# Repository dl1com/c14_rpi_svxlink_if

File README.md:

# c14_rpi_svxlink_if
Raspberry Pi Hat for SVXLink

This repository contains the code and instructions for a custom interface between radio transceivers and a Raspberry Pi running SVXLink.

## Repository contents
The repository contains the following files and directories:

* [c14_rpi_svxlink_if.kicad_pcb](./c14_rpi_svxlink_if.kicad_pcb): the KiCAD project for the custom PCB design.
* [LICENSE.md](./LICENSE.md): the license file for the repository (CC-BY-SA).
* README.md: this file.

## Features

The interface offers the following features:

* Generic DB9 connector for interfacing to transceiver(s)
* Isolated audio rx/tx and signal paths (PTT, Squelch)
* Audio levels can be set with potis
* Fan control output and tacho input
* Telemetry inputs:
  * ADS1115 ADC (i.e. for voltage or RSSI measurement)
  * I2C connectors (i.e. for temperature sensors)

We deliberately decided against placing a soundcard IC on the interface. We use an external, generic USB soundcard instead, as these type of soundcards are very easy and cheap to get on various market places.

## Signal mapping

### DB9 Connector

| Number | Name       |
| ------ | ---------- |
| 1      | SQL_DET-   |
| 2      | SQL_DET+   |
| 3      | RSSI       |
| 4      | RX_AUDIO- |
| 5      | RX_AUDIO+ |
| 6      | PTT_GND   |
| 7      | PTT+      |
| 8      | TX_AUDIO- |
| 9      | TX_AUDIO+ |

### RPi

| GPIO    | Pin | Function   |
| ------- | --- | ---------- |
| GPIO17  | 11  | PTT        |
| GPIO22  | 15  | SQL Det.   |
| GPIO18  | 12  | Fan Ctrl   |
| GPIO24  | 18  | Fan Tacho  |

### Jumper

| JP  | Function                |
| --- | ----------------------- |
| JP1 | Bypass PWM (always on)  |
| JP2 | Enable clipping diodes  |

## Usage

An example project which uses this board can be found at https://charly14.de/svxlink-installation-und-konfiguration/

## License
This repository is licensed under the CC-BY-SA. See the LICENSE file for details.

Concept ist based on the [SVXLink Interface by Aleksander, S65AL](http://lea.hamradio.si/~s57nan/ham_radio/svx_intf_rpi/svx_intf_rpi.html)

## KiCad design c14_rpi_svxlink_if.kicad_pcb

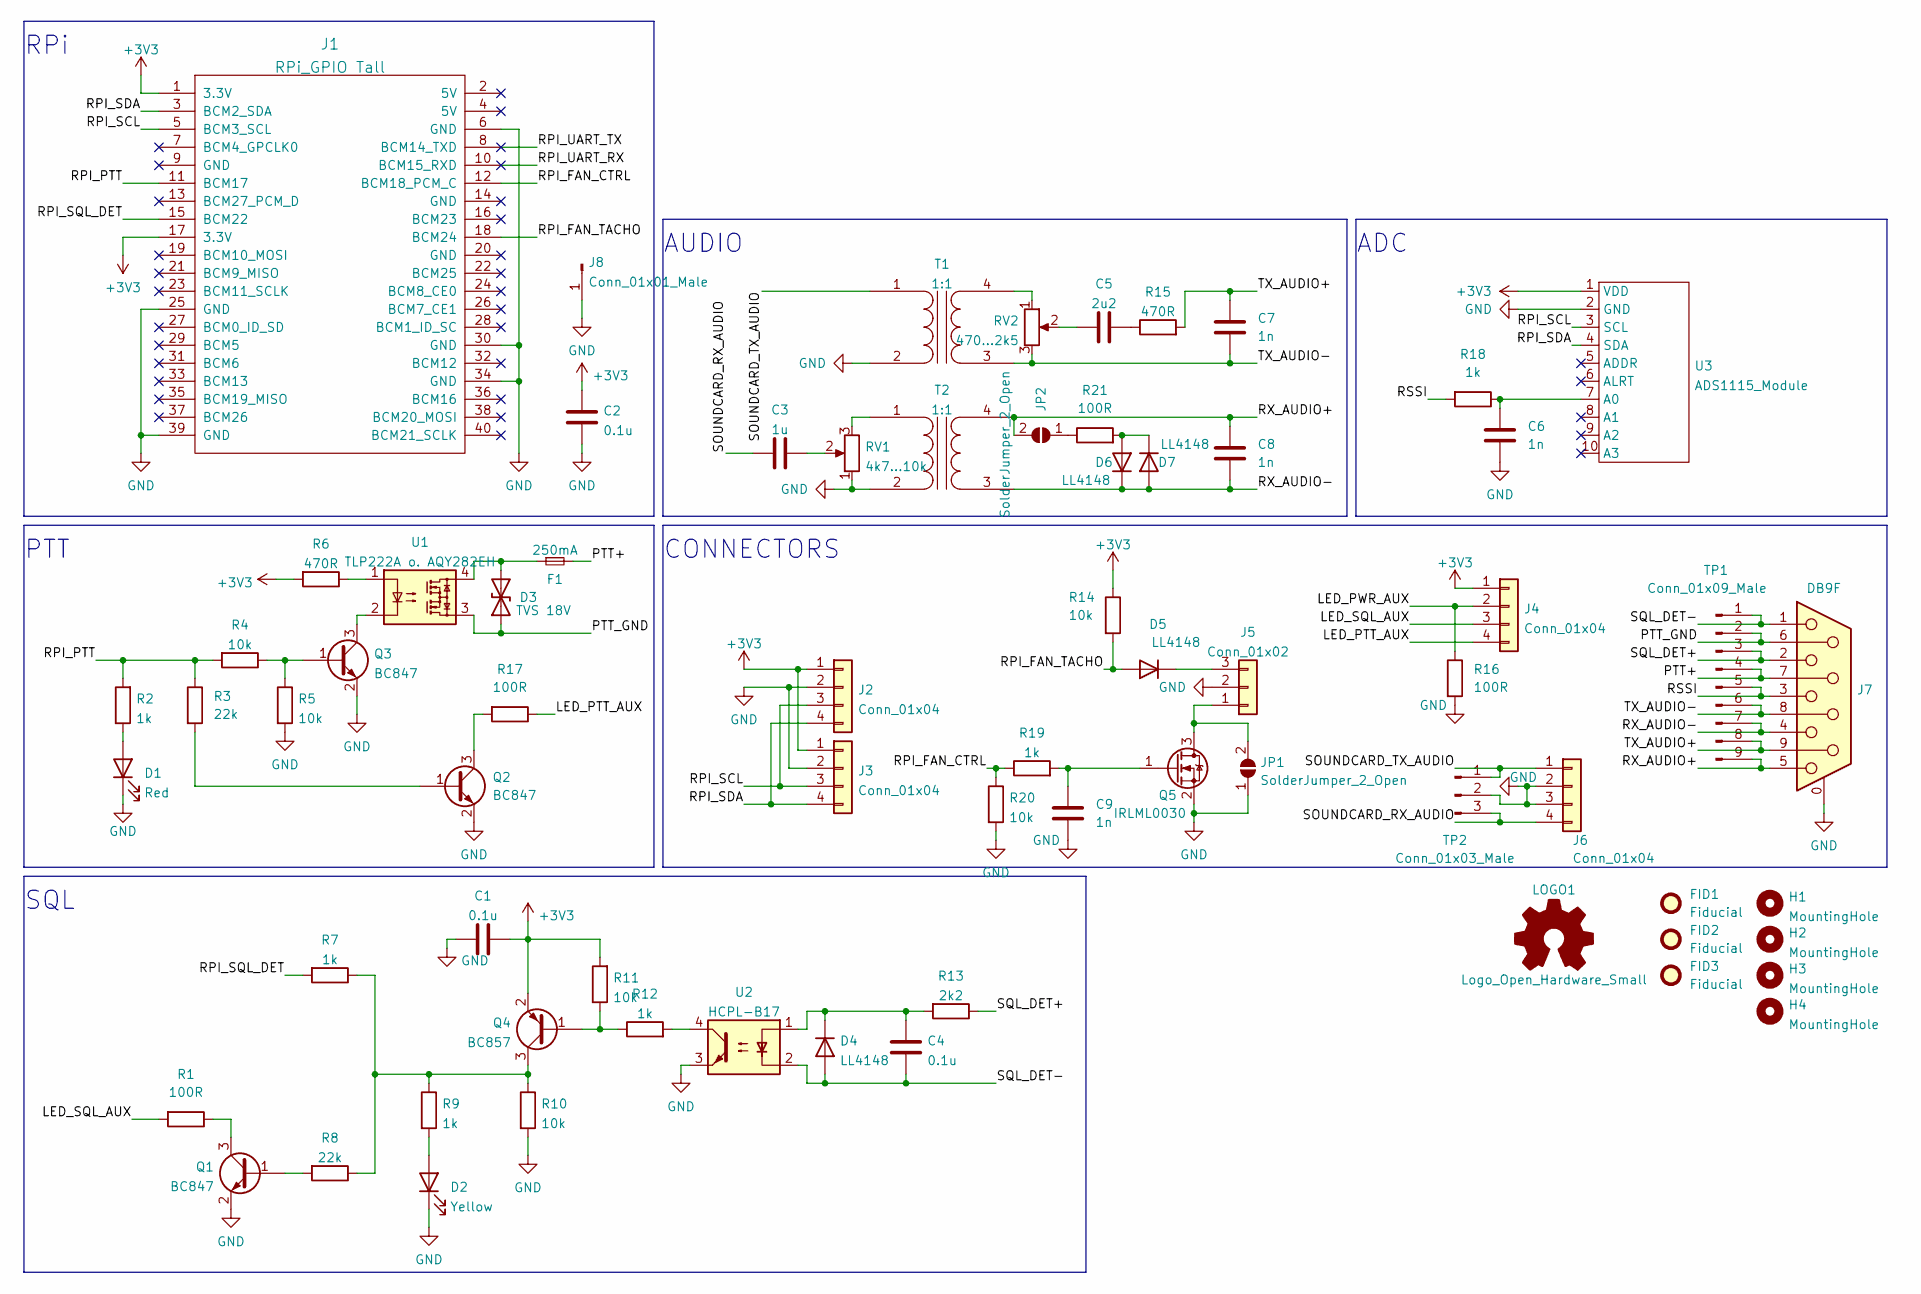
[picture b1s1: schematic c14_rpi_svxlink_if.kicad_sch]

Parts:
C1, C2, C4: 0.1u; C_0805_2012Metric_Pad1.18x1.45mm_HandSolder; PartNr_Mouser 603-CC805KRX7R9BB104
C3: 1u; C_Rect_L7.2mm_W4.5mm_P5.00mm_FKS2_FKP2_MKS2_MKP2; PartNr_Mouser 871-B32529C105J189
C5: 2u2; C_Rect_L7.2mm_W8.5mm_P5.00mm_FKP2_FKP2_MKS2_MKP2; PartNr_Mouser 80-R82CC4220Z370J
C6, C7, C8, C9: 1n; C_0805_2012Metric_Pad1.18x1.45mm_HandSolder; PartNr_Mouser 187-CL21B102KBANNNL
D1: Red; LED_0805_2012Metric_Pad1.15x1.40mm_HandSolder; PartNr_Mouser 755-SML-H12V8TT86C
D2: Yellow; LED_0805_2012Metric_Pad1.15x1.40mm_HandSolder; PartNr_Mouser 755-SML-H12Y8TT86C
D3: TVS 18V; D_SMA-SMB_Universal_Handsoldering; PartNr_Mouser 494-SMBJ18CAE3/TR13
D4, D5, D6, D7: LL4148; D_MiniMELF; PartNr_Mouser 512-LL4148
F1: 250mA; Fuse_1206_3216Metric_Pad1.42x1.75mm_HandSolder; PartNr_Mouser 576-1206L025YR
FID1, FID2, FID3: Fiducial; Fiducial_1mm_Mask3mm
H1, H2, H3, H4: MountingHole; RPi_Hat_Mounting_Hole; PartNr_Mouser --
J1: RPi_GPIO Tall; Pin_Header_Straight_2x20; PartNr_Mouser 485-1992
J2, J3, J4, J6: Conn_01x04; JST_XH_B4B-XH-A_1x04_P2.50mm_Vertical; PartNr_Mouser --
J5: Conn_01x02; JST_XH_B3B-XH-A_1x03_P2.50mm_Vertical
J7: DB9F; DSUB-9_Female_Horizontal_P2.77x2.84mm_EdgePinOffset7.70mm_H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; PartNr_Mouser 523-L77SDE09SA4CH3F
J8: Conn_01x01_Male; PinHeader_1x01_P2.54mm_Vertical
JP1, JP2: SolderJumper_2_Open; SolderJumper-2_P1.3mm_Open_TrianglePad1.0x1.5mm
LOGO1: Logo_Open_Hardware_Small; OSHW-Logo2_9.8x8mm_SilkScreen
Q1, Q2, Q3: BC847; SOT-23; PartNr_Mouser 771-BC847235
Q4: BC857; SOT-23; PartNr_Mouser 771-BC857/T3
Q5: IRLML0030; SOT-23; PartNr_Mouser 942-IRLML0030TRPBF
R1, R16, R17, R21: 100R; R_0805_2012Metric_Pad1.20x1.40mm_HandSolder; PartNr_Mouser 603-RC0805JR-07100RL
R2, R7, R9, R12, R18, R19: 1k; R_0805_2012Metric_Pad1.20x1.40mm_HandSolder; PartNr_Mouser 652-CR0805FX-1001ELF
R3, R8: 22k; R_0805_2012Metric_Pad1.20x1.40mm_HandSolder; PartNr_Mouser 603-RC0805FR-0722KL
R4, R5, R10, R11, R14, R20: 10k; R_0805_2012Metric_Pad1.20x1.40mm_HandSolder; PartNr_Mouser 603-RC0805JR-0710KL
R6, R15: 470R; R_0805_2012Metric_Pad1.20x1.40mm_HandSolder; PartNr_Mouser 652-CR0805FX-4700ELF
R13: 2k2; R_0805_2012Metric_Pad1.20x1.40mm_HandSolder; PartNr_Mouser 652-CR0805FX-2201ELF
RV1: 4k7...10k; Potentiometer_Vishay_TS53YL_Vertical; PartNr_Mouser 72-TS53YL-5K
RV2: 470...2k5; Potentiometer_Vishay_TS53YL_Vertical; PartNr_Mouser 72-TS53YL-500
T1, T2: 1:1; Transformer_NF_ETAL_P3324; PartNr_Mouser 652-LM-NP-1001-B1L
TP1: Conn_01x09_Male; PinHeader_1x09_P1.27mm_Vertical
TP2: Conn_01x03_Male; PinHeader_1x03_P1.27mm_Vertical
U1: TLP222A o. AQY282EH; DIP-4_W7.62mm; PartNr_Mouser AQY282EH
U2: HCPL-B17; DIP-4_W7.62mm; PartNr_Mouser 630-HCPL-817-06DE
U3: ADS1115_Module; ADS1115 Module; PartNr_Mouser --

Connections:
+3V3: C1.2, C2.1, J1.1 (3.3V), J1.17 (3.3V), J2.1, J3.1, J4.1, Q4.2 (E), R6.2, R11.2, R14.1, U3.1 (VDD)
/LED_PTT_AUX: J4.4, R17.1
/LED_PWR_AUX: J4.2, R16.1
/LED_SQL_AUX: J4.3, R1.2
/PTT+: F1.2, J7.7, TP1.4
/PTT_GND: D3.1 (A1), J7.6, TP1.2, U1.3
/RPI_FAN_CTRL: J1.12 (BCM18_PCM_C), R19.1, R20.1
/RPI_FAN_TACHO: D5.2 (A), J1.18 (BCM24), R14.2
/RPI_PTT: J1.11 (BCM17), R2.2, R3.1, R4.2
/RPI_SCL: J1.5 (BCM3_SCL), J2.3, J3.3, U3.3 (SCL)
/RPI_SDA: J1.3 (BCM2_SDA), J2.4, J3.4, U3.4 (SDA)
/RPI_SQL_DET: J1.15 (BCM22), R7.2
/RPI_UART_RX: J1.10 (BCM15_RXD)
/RPI_UART_TX: J1.8 (BCM14_TXD)
/RSSI: J7.3, R18.2, TP1.5
/RX_AUDIO+: C8.2, J7.5, JP2.2 (B), T2.4 (SB), TP1.9
/RX_AUDIO-: C8.1, D6.1 (K), D7.2 (A), J7.4, T2.3 (SA), TP1.7
/SOUNDCARD_RX_AUDIO: C3.2, J6.4, TP2.3
/SOUNDCARD_TX_AUDIO: J6.1, T1.1 (AA), TP2.1
/SQL_DET+: J7.2, R13.1, TP1.3
/SQL_DET-: C4.1, D4.2 (A), J7.1, TP1.1, U2.2
/TX_AUDIO+: C7.2, J7.9, R15.2, TP1.8
/TX_AUDIO-: C7.1, J7.8, RV2.3, T1.3 (SA), TP1.6
GND: C1.1, C2.2, C6.1, C9.1, D1.1 (K), D2.1 (K), J1.6 (GND), J1.25 (GND), J1.30 (GND), J1.34 (GND), J1.39 (GND), J2.2, J3.2, J5.2, J6.2, J6.3, J7.0 (PAD), J8.1, JP1.1 (A), Q1.2 (E), Q2.2 (E), Q3.2 (E), Q5.2 (S), R5.2, R10.2, R16.2, R20.2, RV1.1, T1.2 (AB), T2.2 (AB), TP2.2, U2.3, U3.2 (GND)
unnamed: C3.1, RV1.2
unnamed: C4.2, D4.1 (K), R13.2, U2.1
unnamed: C5.1, R15.1
unnamed: C5.2, RV2.2
unnamed: C6.2, R18.1, U3.7 (A0)
unnamed: D1.2 (A), R2.1
unnamed: D2.2 (A), R9.2
unnamed: D3.2 (A2), F1.1, U1.4
unnamed: D5.1 (K), J5.3
unnamed: D6.2 (A), D7.1 (K), R21.2
unnamed: J5.1, JP1.2 (B), Q5.3 (D)
unnamed: JP2.1 (A), R21.1
unnamed: Q1.1 (B), R8.2
unnamed: Q1.3 (C), R1.1
unnamed: Q2.1 (B), R3.2
unnamed: Q2.3 (C), R17.2
unnamed: Q3.1 (B), R4.1, R5.1
unnamed: Q3.3 (C), U1.2
unnamed: Q4.1 (B), R11.1, R12.1
unnamed: Q4.3 (C), R7.1, R8.1, R9.1, R10.1
unnamed: C9.2, Q5.1 (G), R19.2
unnamed: R6.1, U1.1
unnamed: R12.2, U2.4
unnamed: RV1.3, T2.1 (AA)
unnamed: RV2.1, T1.4 (SB)

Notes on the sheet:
ADC
CONNECTORS
SQL
RPi
PTT
AUDIO

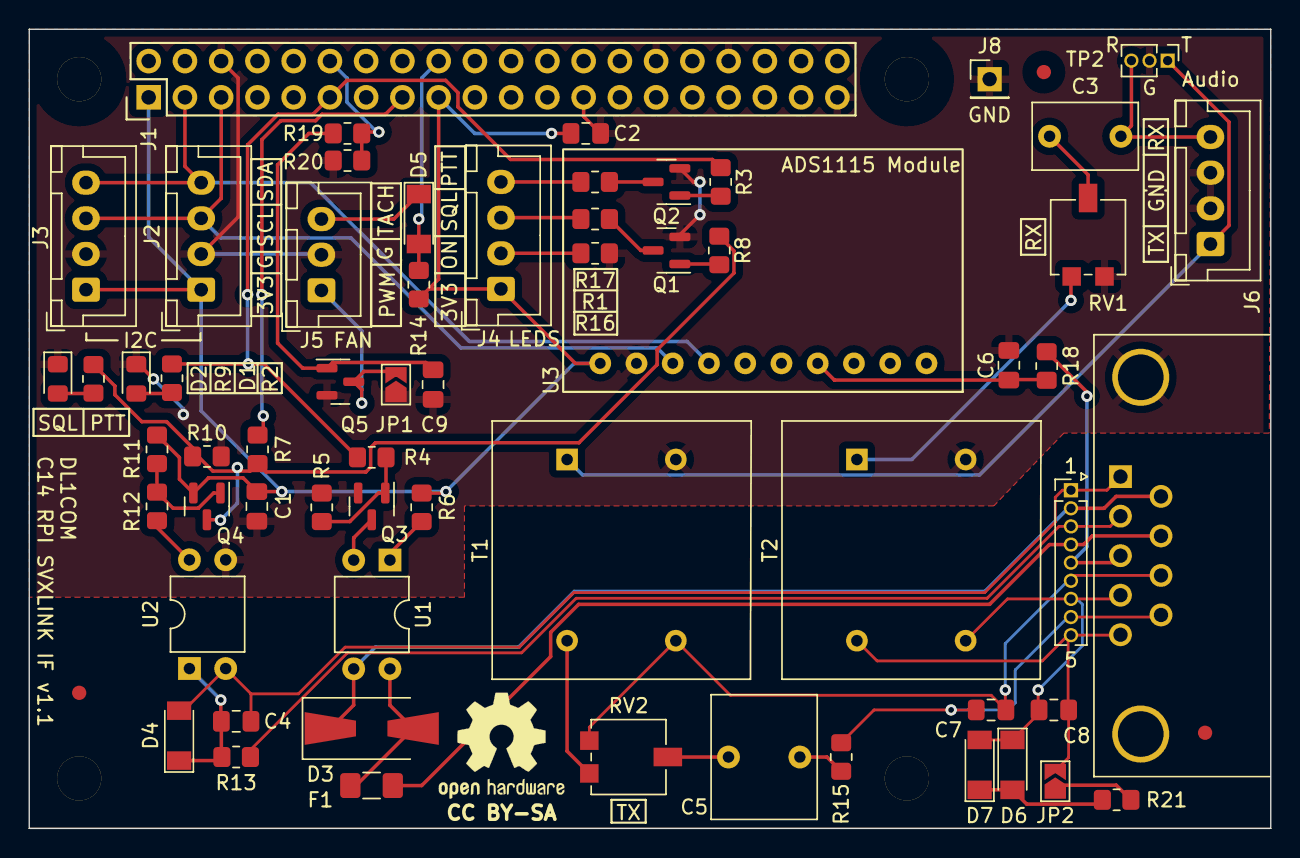
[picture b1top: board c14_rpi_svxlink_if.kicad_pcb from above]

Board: 2 copper layers, 87.0 x 56.0 mm, 70 parts (0 on the bottom side), 47 nets.

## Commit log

2022-02-28 Layout fertig, DRC und Review fehlen
2022-04-09 Extending gitignore
2022-04-09 Small preproduction changes
2022-04-09 Fix: Correct Footprint for J7 (M->F)
2022-04-09 Added Fiducials
2022-04-09 Add License and OSHW logo
2022-04-09 Add Open Collector for Fan Ctrl
2022-09-15 Neue Teile platziert, pre-1.1 bereit fuer Review
2022-09-18 ready for production
2022-11-24 Changelog v1.1
2022-11-24 last changes for 1.1
2022-11-26 Add releases folder
2023-03-19 Update README.md
    name license file with extension and link to the files for quicker access
